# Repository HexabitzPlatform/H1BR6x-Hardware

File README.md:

# H1BR6x-Hardware
Hexabitz Micro SD Memory Card Module Hardware Design

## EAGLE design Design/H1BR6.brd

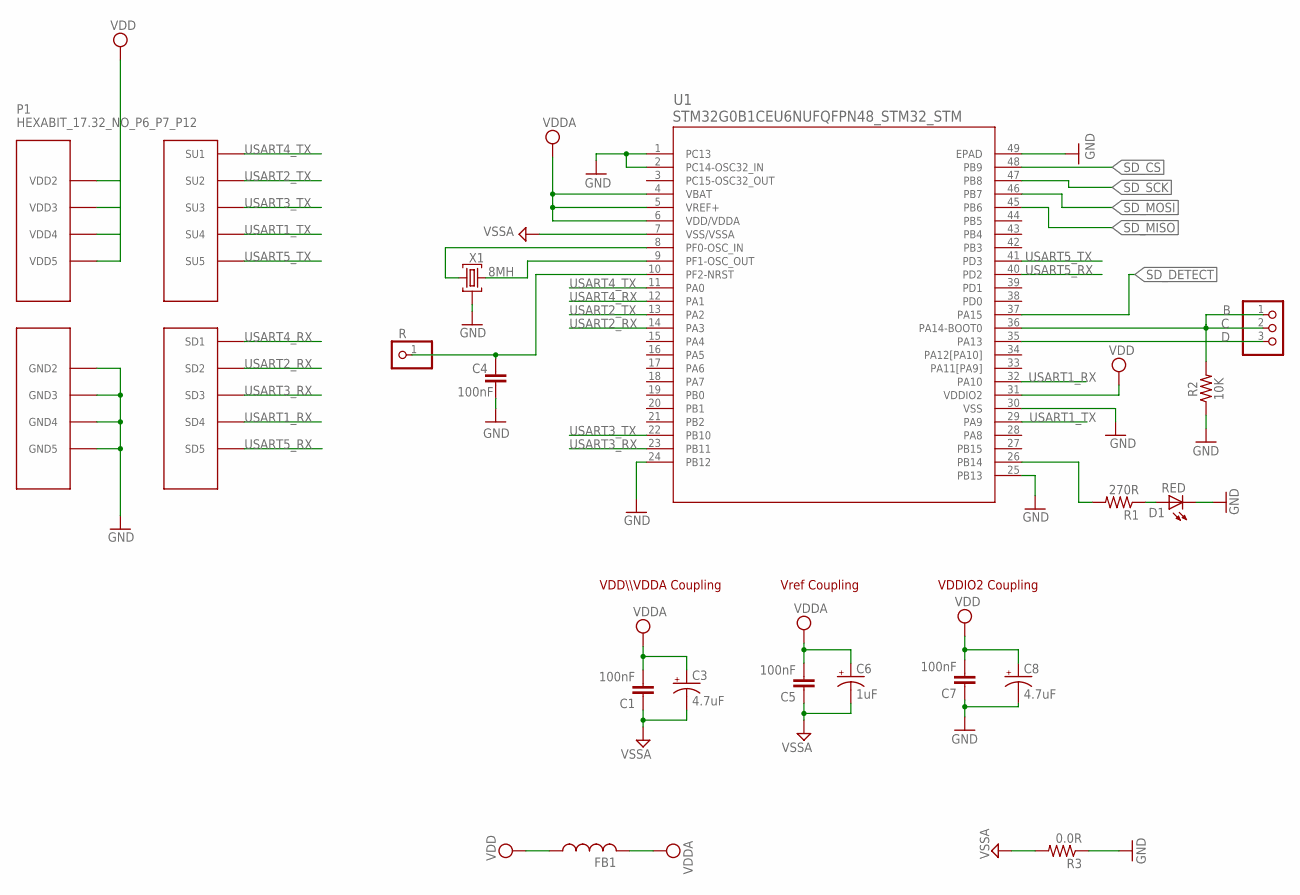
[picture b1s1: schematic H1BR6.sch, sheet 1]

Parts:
C1, C5, C7: 100nF; C-0603; TOLERANCE 10%; VOLTAGE_RATING 16.0 V; MPN '0603YC104K4T2A
C3: 4.7uF; C-0805-POL; TOLERANCE 20%; VOLTAGE_RATING 10.0 V; MPN '10TPU4R7MSI
C4: 100nF; C-0603; TOLERANCE 10%; VOLTAGE_RATING 16.0 V; MPN 0603YC104K4T2A
C6: 1uF; C-0805-POL; TOLERANCE 20%; VOLTAGE_RATING 10.0 V; MPN 'CC0805KKX7R7BB105
C8: 4.7uF; C-0805-POL; TOLERANCE 10%; VOLTAGE_RATING 16.0 V; MPN '10TPU4R7MSI
D1: RED; VLMS1300-GS08
FB1: FB-TDK_MMZ1608Y300B; MPN MMZ1608Y300BTA00
J4: PINHD-1X1; 1X01
JP1: PINHD-1X3; 1X03
P1: HEXABIT_17.32_NO_P6_P7_P12
R1: 270R; R-0603; MPN 'ERJ-3GEYJ271V
R2: 10K; R-0603; MPN '060300J0103T5E
R3: 0.0R; R-0603; MPN RC0603JR-070RL
U1: STM32G0B1CEU6NUFQFPN48_STM32_STM; UFQFPN48_STM32_STM
X1: 8MH; XTALL_CSTCE8M00G52; MPN CSTNE8M00G550000R0

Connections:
C: JP1.1, JP1.2, R2.2, U1.36 (PA14-BOOT0)
D: JP1.3, U1.35 (PA13)
GND: C4.1, C7.1, C8.2 (-), D1.C, P1.PAD_PD8 (GND2), P1.PAD_PD9 (GND3), P1.PAD_PD10 (GND4), P1.PAD_PD11 (GND5), R2.1, R3.1, U1.1 (PC13), U1.2 (PC14-OSC32_IN), U1.24 (PB12), U1.25 (PB13), U1.30 (VSS), U1.49 (EPAD), X1.P$2 (2); also elsewhere on the board
GND1: C1.1, C3.2 (-), C5.1, C6.2 (-), R3.2, U1.7 (VSS/VSSA)
unnamed: U1.8 (PF0-OSC_IN), X1.P$3 (3)
unnamed: U1.9 (PF1-OSC_OUT), X1.P$1 (1)
unnamed: R1.2, U1.26 (PB14)
unnamed: D1.A, R1.1
R: C4.2, J4.1, U1.10 (PF2-NRST)
SD_CS: U1.48 (PB9); also elsewhere on the board
SD_DETECT: U1.37 (PA15); also elsewhere on the board
SD_MISO: U1.45 (PB6); also elsewhere on the board
SD_MOSI: U1.46 (PB7); also elsewhere on the board
SD_SCK: U1.47 (PB8); also elsewhere on the board
USART1_RX: P1.PAD_PD4 (SD4), U1.32 (PA10)
USART1_TX: P1.PAD_PU4 (SU4), U1.29 (PA9)
USART2_RX: P1.PAD_PD2 (SD2), U1.14 (PA3)
USART2_TX: P1.PAD_PU2 (SU2), U1.13 (PA2)
USART3_RX: P1.PAD_PD3 (SD3), U1.23 (PB11)
USART3_TX: P1.PAD_PU3 (SU3), U1.22 (PB10)
USART4_RX: P1.PAD_PD1 (SD1), U1.12 (PA1)
USART4_TX: P1.PAD_PU1 (SU1), U1.11 (PA0)
USART5_RX: P1.PAD_PD5 (SD5), U1.40 (PD2)
USART5_TX: P1.PAD_PU5 (SU5), U1.41 (PD3)
VCC: C1.2, C3.1 (+), C5.2, C6.1 (+), FB1.2, U1.4 (VBAT), U1.5 (VREF+), U1.6 (VDD/VDDA)
VDD: C7.2, C8.1 (+), FB1.1, P1.PAD_PU8 (VDD2), P1.PAD_PU9 (VDD3), P1.PAD_PU10 (VDD4), P1.PAD_PU11 (VDD5), U1.31 (VDDIO2); also elsewhere on the board

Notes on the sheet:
VDDIO2 Coupling
VDD\\\VDDA Coupling
Vref Coupling

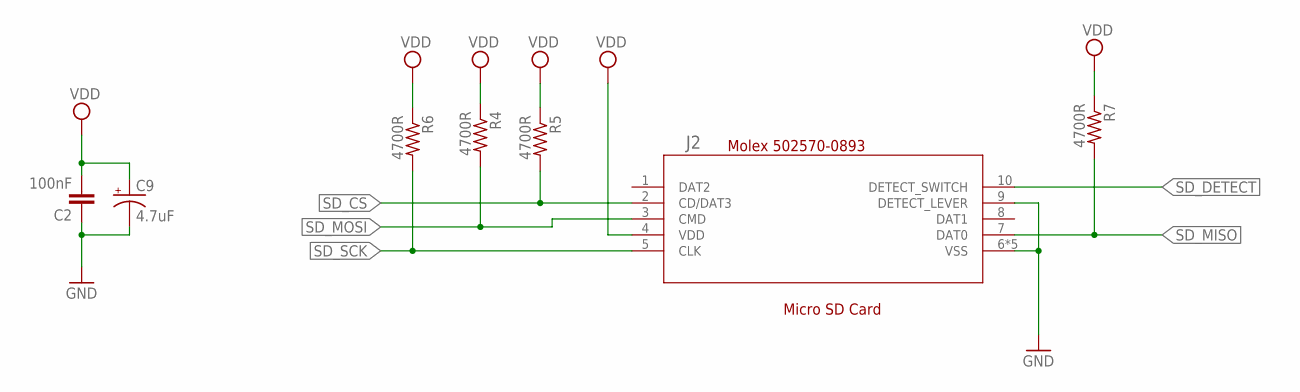
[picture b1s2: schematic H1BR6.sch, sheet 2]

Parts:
C2: 100nF; C-0603; TOLERANCE 10%; VOLTAGE_RATING 16.0 V; MPN '0603YC104K4T2A
C9: 4.7uF; C-0805-POL; TOLERANCE 20%; VOLTAGE_RATING 10.0 V; MPN '10TPU4R7MSI
J2: 5025700893502570-0893_MOL; 502570-0893_MOL
R4, R5, R6, R7: 4700R; R-0603; TOLERANCE 5%; MPN RC0603JR-074K7L

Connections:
GND: C2.1, C9.2 (-), J2.6 (VSS), J2.9 (DETECT_LEVER), J2.11 (VSS), J2.12 (VSS), J2.13 (VSS), J2.14 (VSS); also elsewhere on the board
SD_CS: J2.2 (CD/DAT3), R5.2; also elsewhere on the board
SD_DETECT: J2.10 (DETECT_SWITCH); also elsewhere on the board
SD_MISO: J2.7 (DAT0), R7.2; also elsewhere on the board
SD_MOSI: J2.3 (CMD), R4.2; also elsewhere on the board
SD_SCK: J2.5 (CLK), R6.2; also elsewhere on the board
VDD: C2.2, C9.1 (+), J2.4 (VDD), R4.1, R5.1, R6.1, R7.1; also elsewhere on the board

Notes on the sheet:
Micro SD Card
Molex 502570-0893

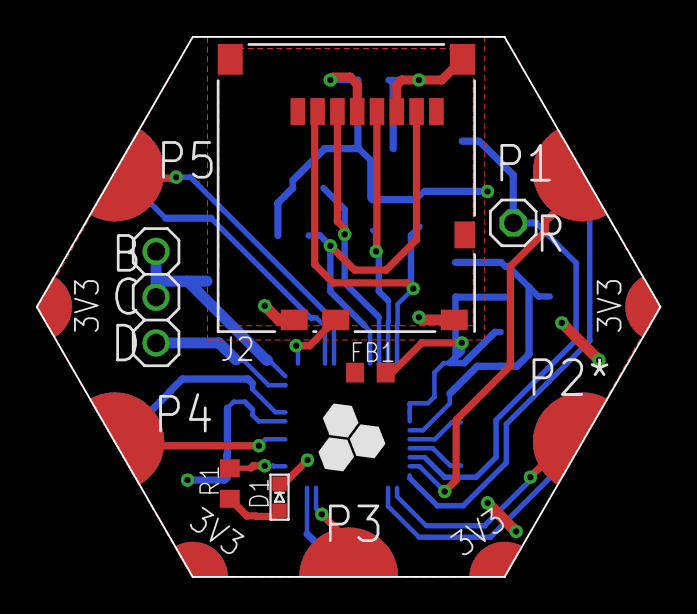
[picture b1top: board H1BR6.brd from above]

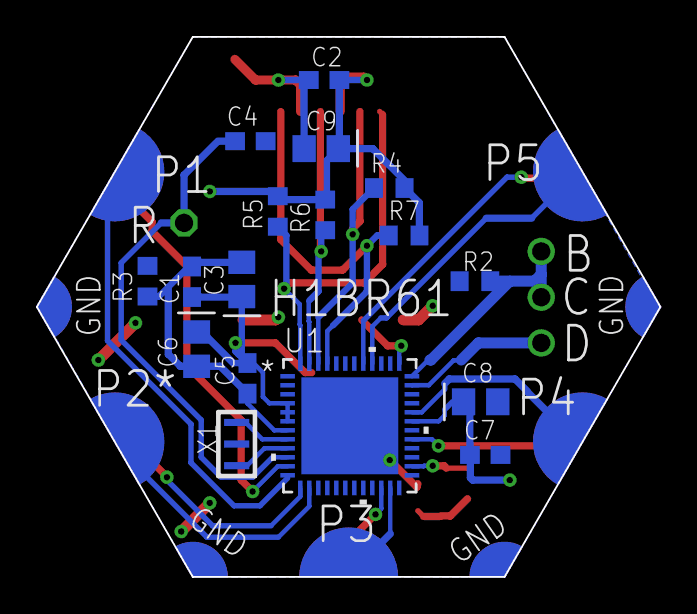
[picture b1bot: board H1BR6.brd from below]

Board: 2 copper layers, 34.6 x 30.0 mm, 24 parts (17 on the bottom side), 26 nets.

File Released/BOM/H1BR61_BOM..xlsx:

Qty | Comment | Designator | Description | MFN | MPN | OCTOPART_URL
1 | 5025700893502570-0893_MOL | J2 | 1.10mm Pitch microSD Memory Card Connector, Normal Mount Surface Mount | Molex | 502570-0893 | https://octopart.com/502570-0893-molex-42270318?r=sp
1 | FB-TDK_MMZ1608Y300BTA00 | FB1 | Ind chip Bead Multi-Layer 30 ohms 25% 100MHZ Ferrite 1,5A 0603Punched paper T/R | TDK | MMZ1608Y300BTA00 | https://octopart.com/mmz1608y300bta00-tdk-7906990?r=sp
1 | PINHD-1X1 | J4 | PCB Header, Unshrouded, Thru 02 Straight Header, .101, AMPMODU Mod II Series | TE Connectivity | 87227-1 | https://octopart.com/87227-1-te+connectivity-39512052?r=sp
1 | PINHD-1X3 | JP1 | Conn Unshrouded Header HDR 3 POS 2.54mm Solder ST Top Entry Thru-Hole Carton | TE Connectivity | 5-146281-3 | https://octopart.com/5-146281-3-te+connectivity+%2F+amp-3974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
1 | 0.0R | R3 | RES SMD 0.0OHM JUMPER 1/10W 0603 | YAGEO [VR] | RC0603JR-070RL | https://octopart.com/rc0603jr-070rl-yageo-1241539?r=sp
5 | 100nF | C1,C2,C4,C5,C7 | CAP CER 0,1UF 16V X7R 0603 | AVX CORPORATION | 0603YC104K4T2A | https://octopart.com/0603yc104k4t2a-avx+interconnect+%2F+elc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
1 | 10K | R2 | RES 10 K OHM 5% 0603 | Vishay | CRCW060310K0JNEB | https://octopart.com/crcw060310k0jneb-vishay-46603269
1 | 1uF | C6 | CAP CER 1UF 16V X7R 0805 | YAGEO [VA] | CC0805KKX7R7BB105 | https://octopart.com/cc0805kkx7r7bb105-yageo-8376555?r=sp
1 | 270R | R1 | Thick Film Resistors - SMD 0603 270ohms 5% Tol | Panasonic | ERJ-3GEYJ271V | https://octopart.com/erj-3geyj271v-panasonic-55560546?r=sp
3 | 4.7uF | C3,C8,C9 | CAP TANT 4.7UF 10V 20% 0805 | Panasonic | 10TPU4R7MSI | https://octopart.com/10tpu4r7msi-panasonic-29487748?r=sp
4 | 4700R | R4,R5,R6,R7 | Thick Film Resistors - SMD 0603 | YAGED [VA] | RC0603JR-074K7L | https://octopart.com/rc0603jr-074k7l-yageo-55458509?r=sp
1 | XTALL_CSTCE8M00G52 | X1 | 8,0000MHZ 33pF SMD MURATA Resonators | Murata | CSTNE8M00G550000R0 | https://octopart.com/cstne8m00g550000r0-murata-91406934?r=sp
1 | VLMS1300-GS08 | D1 | Red 0603 130آ° Clear 54 mcd 2 V Surface Mount ChipLED ; | Vishay | VLMS1300-GS08 | https://octopart.com/vlms1300-gs08-vishay-21709201?r=sp&s=0n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
1 | STM32G0B1CEU6N | U1 | MCU 32-Bit ARM Cortex-M0+ RISC 512kByte Flash 1.7V to 3.6V 48-Pin UFQFPN Tray | STMicroelectronics | STM32G0B1CEU6N | https://octopart.com/stm32g0b1ceu6n-stmicroelectronics-11636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

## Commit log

2022-04-30 -Changing the MC with STM32G0
2022-08-23 Correcting Schematic file
2023-02-16 -Correcting some documentaion issues
2024-03-07 Fix some documentation issues
2024-03-07 Fix readme file

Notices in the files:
parts and their libraries:
COPYRIGHT: Copyright (C) 2022 Ultra Librarian. All rights reserved.
